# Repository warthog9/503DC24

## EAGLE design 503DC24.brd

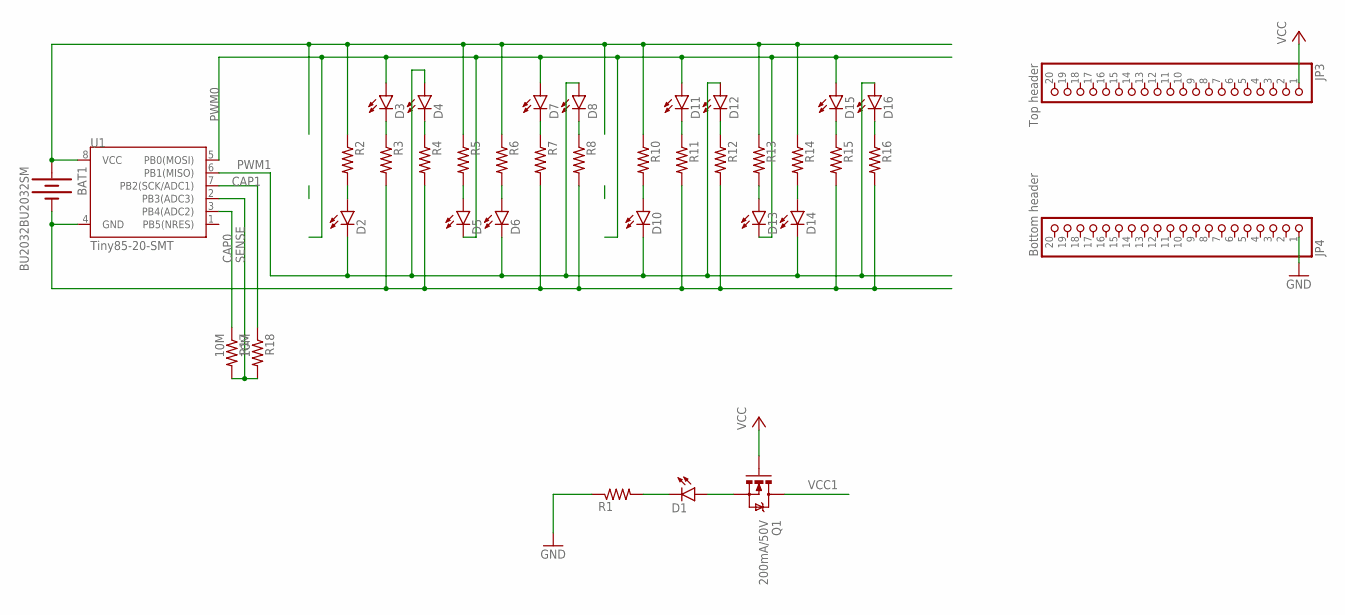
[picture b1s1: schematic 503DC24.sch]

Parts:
BAT1: BU2032BU2032SM; BU2032SM
D1, D2, D3, D4, D5, D6, D7, D8, D10, D11, D12, D13, D14, D15, D16: LED1206-BOTTOM-SMALL_SILK; LED-REV-MNT-SMALLSILK
JP3: Top header; 1X20
JP4: Bottom header; 1X20
Q1: 200mA/50V; SOT23-3
R1, R2, R3, R4, R5, R6, R7, R8, R10, R11, R12, R13, R14, R15, R16: RESISTOR1206; 1206
R17, R18: 10M; 0805
U1: Tiny85-20-SMT; SO08-EIAJ

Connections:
CAP0: R17.1, U1.3 (PB4(ADC2))
CAP1: R18.1, U1.7 (PB2(SCK/ADC1))
GND: JP4.1, R1.1
GND1: BAT1.P- (-), R3.2, R4.2, R7.2, R8.2, R11.2, R12.2, R15.2, R16.2, U1.4 (GND)
unnamed: D2.A, R2.2
unnamed: D3.C, R3.1
unnamed: D4.C, R4.1
unnamed: D5.A, R5.2
unnamed: D6.A, R6.2
unnamed: D16.C, R16.1
unnamed: D15.C, R15.1
unnamed: D10.A, R10.2
unnamed: D12.C, R12.1
unnamed: D11.C, R11.1
unnamed: D8.C, R8.1
unnamed: D7.C, R7.1
unnamed: D13.A, R13.2
unnamed: D14.A, R14.2
unnamed: D1.A, Q1.2 (S)
unnamed: D1.C, R1.2
PWM0: D3.A, D5.C, D7.A, D11.A, D13.C, D15.A, U1.5 (PB0(MOSI))
PWM1: D2.C, D4.A, D6.C, D8.A, D10.C, D12.A, D14.C, D16.A, U1.6 (PB1(MISO))
SENSE: R17.2, R18.2, U1.2 (PB3(ADC3))
VCC: JP3.1, Q1.1 (G)
VCC1: BAT1.P+ (+), Q1.3 (D), R2.1, R5.1, R6.1, R10.1, R13.1, R14.1, U1.8 (VCC)

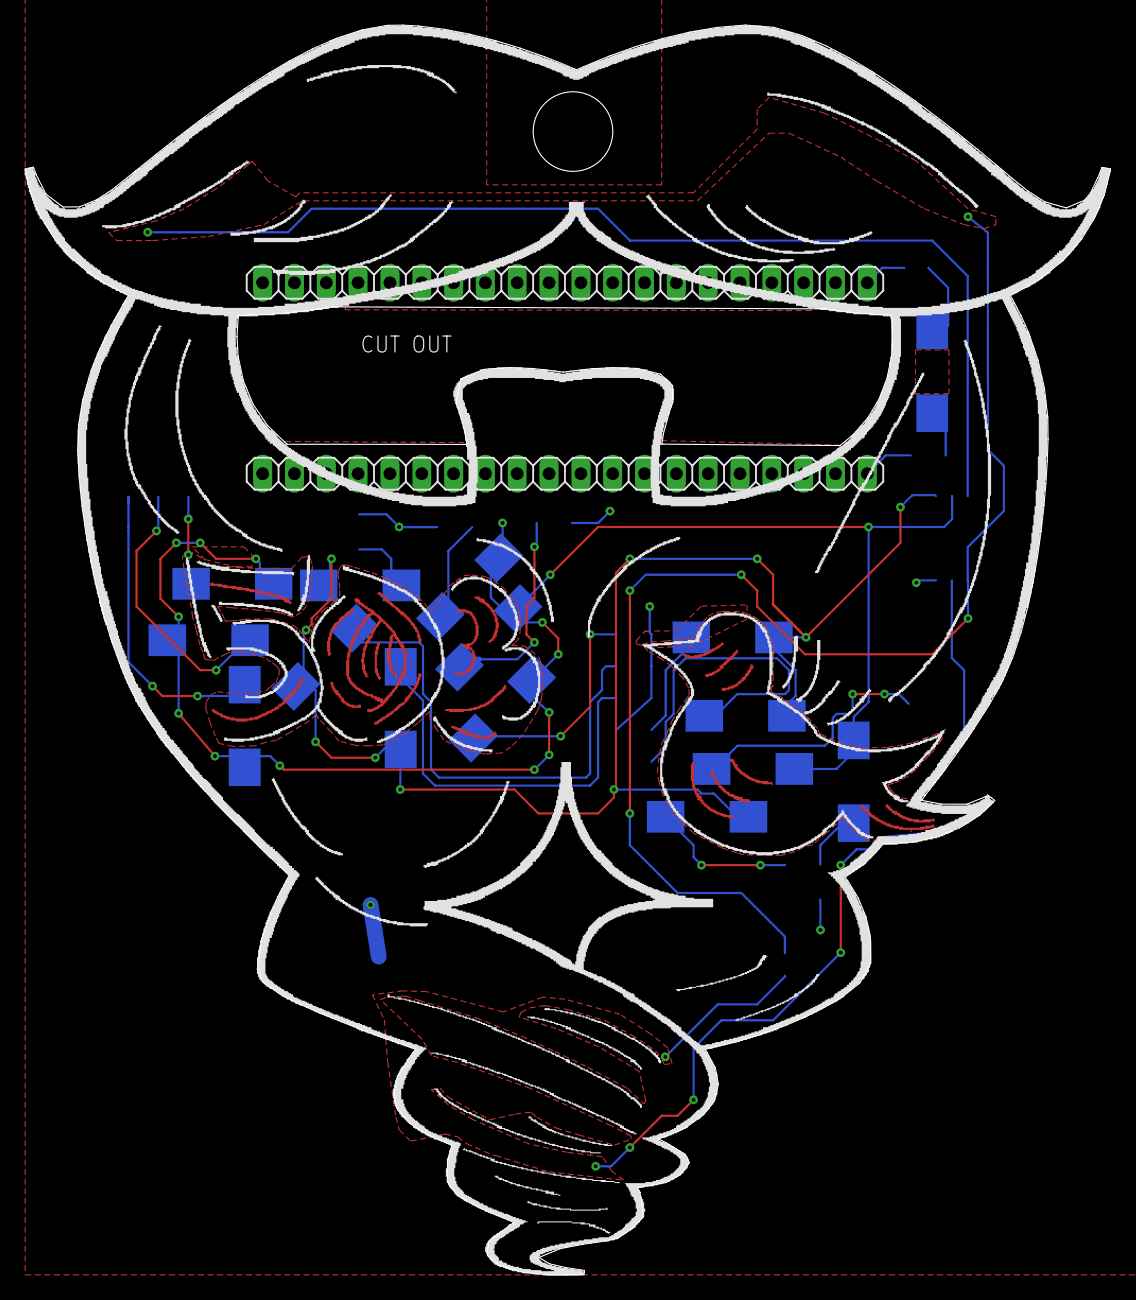
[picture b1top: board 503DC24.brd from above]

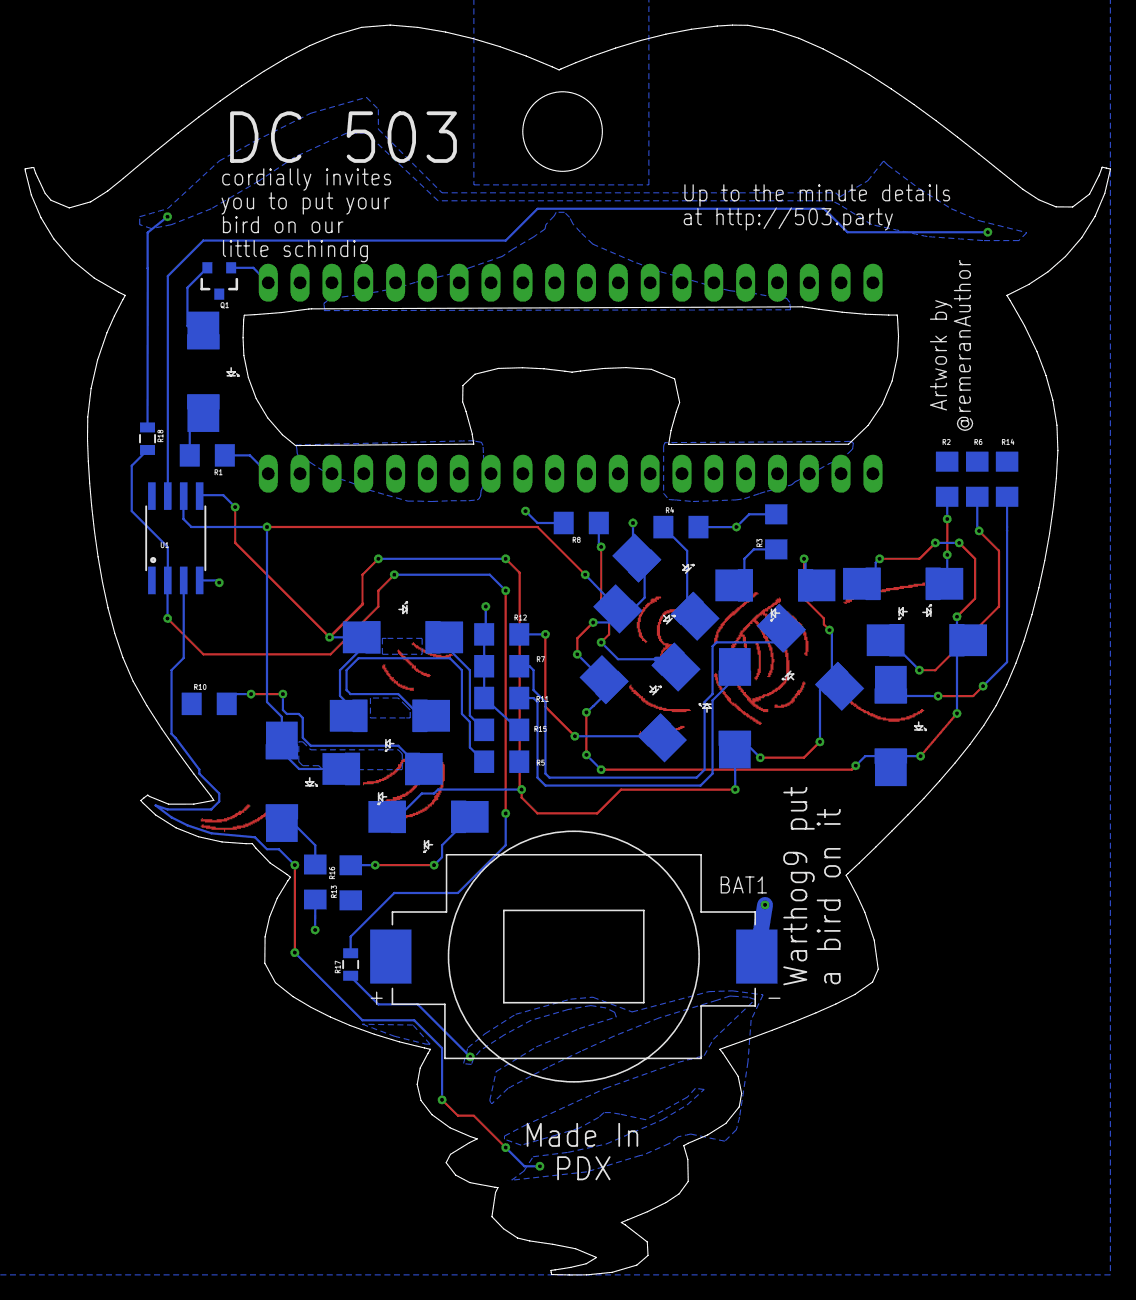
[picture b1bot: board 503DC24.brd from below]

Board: 2 copper layers, 86.6 x 99.8 mm, 37 parts (35 on the bottom side), 25 nets.

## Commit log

2017-01-02 Initial commit with the basics
2017-01-02 Adding Board Schematic, Layout, & additional files for design
2017-01-02 Adding the License File
2017-01-02 Adding the beard colateral
2017-01-18 Basic BOM pulled from the Digikey order for the run
    This has one "gotcha" in that the LEDs we used are not easily
    obtainable. We used white ones, however there's a red version
    that's more easily available so I'm substituting that in for ease
    of people finding a part that should work.
2017-06-25 BOM for the 503DC24 boards
2017-06-25 Adding in the gerbers for the production run

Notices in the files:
parts and their libraries:
SparkFun-DigitalIC: Licensing: Creative Commons ShareAlike 4.0 International - https://creativecommons.org/licenses/by-sa/4.0
